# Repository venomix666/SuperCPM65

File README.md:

# SuperCPM65
SNES cartrige for CP/M-65, still an untested work in progress

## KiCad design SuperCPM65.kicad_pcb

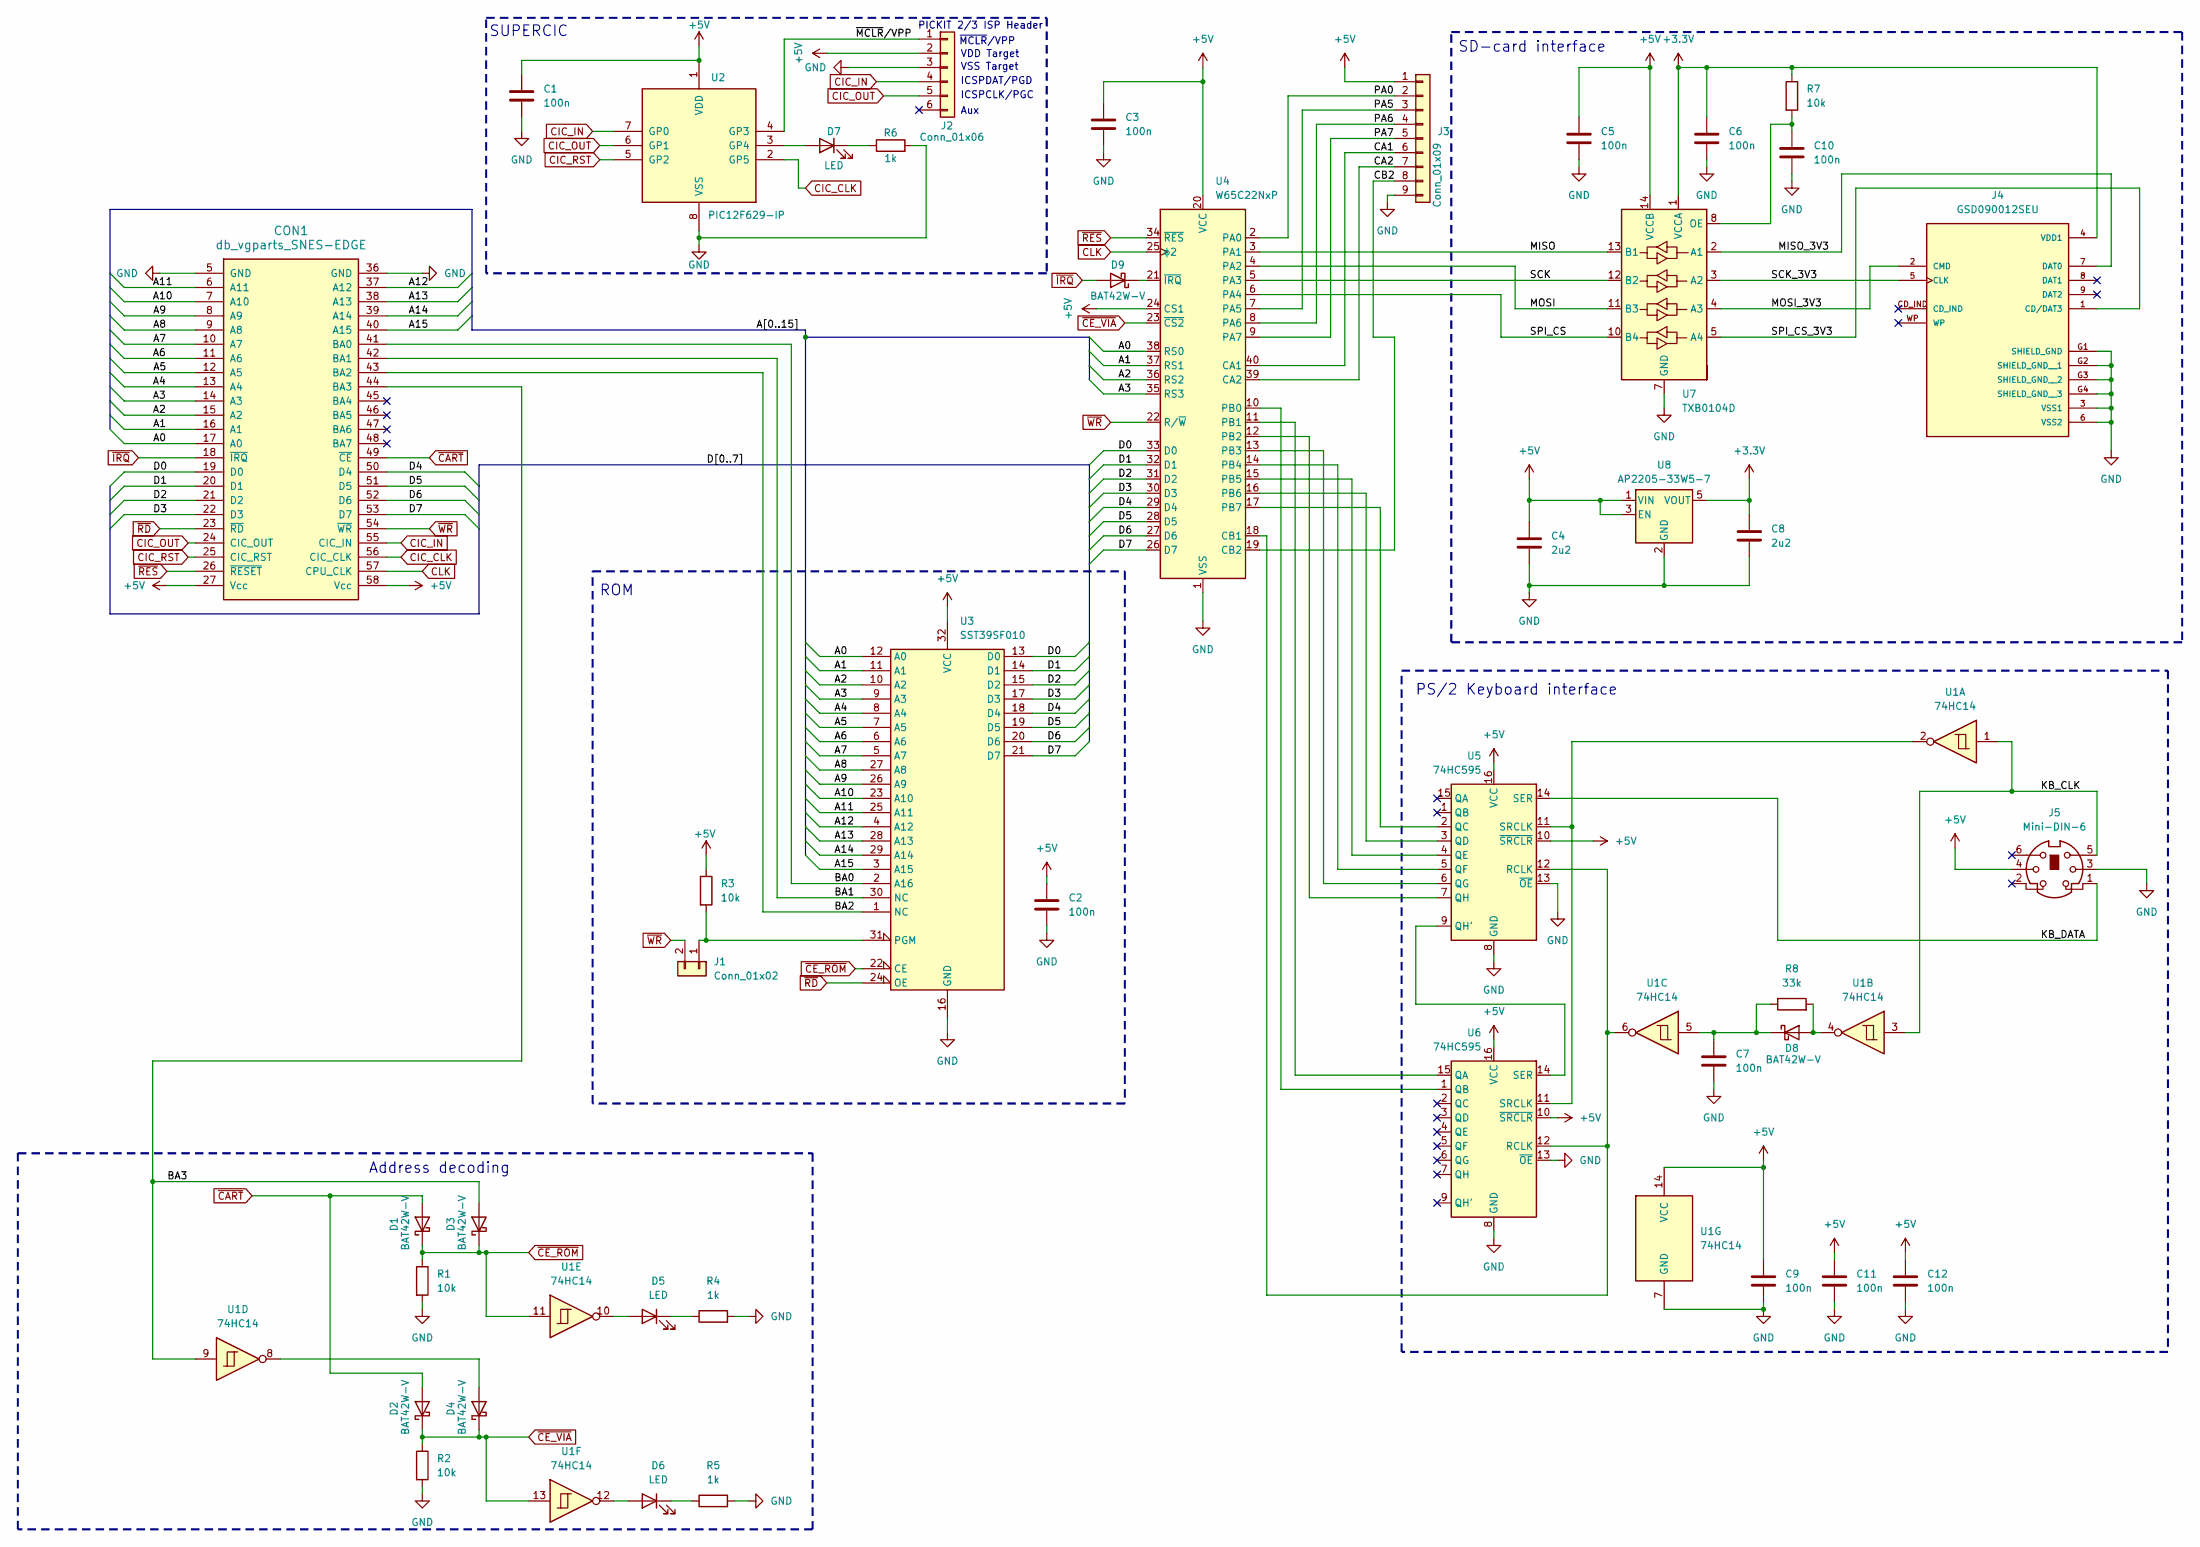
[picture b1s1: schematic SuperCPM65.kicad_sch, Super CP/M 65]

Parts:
C1, C2, C3, C5, C6, C7, C9, C10, C11, C12: 100n; C_0805_2012Metric_Pad1.18x1.45mm_HandSolder
C4, C8: 2u2; C_0805_2012Metric_Pad1.18x1.45mm_HandSolder
CON1: db_vgparts_SNES-EDGE; SNES-EDGE-Bigger
D1, D2, D3, D4, D8, D9: BAT42W-V; D_SOD-123
D5, D6, D7: LED; LED_0805_2012Metric
J1: Conn_01x02; PinHeader_1x02_P2.54mm_Vertical
J2: Conn_01x06; PinHeader_1x06_P2.54mm_Vertical
J3: Conn_01x09; PinHeader_1x09_P2.54mm_Vertical
J4: GSD090012SEU; AMPHENOL_GSD090012SEU; PARTREV E
J5: Mini-DIN-6; TE 5749266-1
R1, R2, R3, R7: 10k; R_0805_2012Metric_Pad1.20x1.40mm_HandSolder
R4, R5, R6: 1k; R_0805_2012Metric_Pad1.20x1.40mm_HandSolder
R8: 33k; R_0805_2012Metric_Pad1.20x1.40mm_HandSolder
U1: 74HC14; SOIC-14_3.9x8.7mm_P1.27mm
U2: PIC12F629-IP; DIP-8_W7.62mm_Socket
U3: SST39SF010; DIP-32_W15.24mm_Socket
U4: W65C22NxP; DIP-40_W15.24mm
U5, U6: 74HC595; SOIC-16_3.9x9.9mm_P1.27mm
U7: TXB0104D; SOIC-14_3.9x8.7mm_P1.27mm
U8: AP2205-33W5-7; SOT-23-5

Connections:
+3.3V: C6.1, C8.1, J4.4 (VDD1), R7.1, U7.1 (VCCA), U8.5 (VOUT)
+5V: C1.1, C2.1, C3.1, C4.1, C5.1, C9.1, C11.1, C12.1, CON1.27 (Vcc), CON1.58 (Vcc), J2.2, J3.1, J5.4, R3.1, U1.14 (VCC), U2.1 (VDD), U3.32 (VCC), U4.20 (VCC), U4.24 (CS1), U5.10 (~SRCLR), U5.16 (VCC), U6.10 (~SRCLR), U6.16 (VCC), U7.14 (VCCB), U8.1 (VIN), U8.3 (EN)
/A0: CON1.17 (A0), U3.12 (A0), U4.38 (RS0)
/A1: CON1.16 (A1), U3.11 (A1), U4.37 (RS1)
/A2: CON1.15 (A2), U3.10 (A2), U4.36 (RS2)
/A3: CON1.14 (A3), U3.9 (A3), U4.35 (RS3)
/A4: CON1.13 (A4), U3.8 (A4)
/A5: CON1.12 (A5), U3.7 (A5)
/A6: CON1.11 (A6), U3.6 (A6)
/A7: CON1.10 (A7), U3.5 (A7)
/A8: CON1.9 (A8), U3.27 (A8)
/A9: CON1.8 (A9), U3.26 (A9)
/A10: CON1.7 (A10), U3.23 (A10)
/A11: CON1.6 (A11), U3.25 (A11)
/A12: CON1.37 (A12), U3.4 (A12)
/A13: CON1.38 (A13), U3.28 (A13)
/A14: CON1.39 (A14), U3.29 (A14)
/A15: CON1.40 (A15), U3.3 (A15)
/BA0: CON1.41 (BA0), U3.2 (A16)
/BA1: CON1.42 (BA1), U3.30 (NC)
/BA2: CON1.43 (BA2), U3.1 (NC)
/BA3: CON1.44 (BA3), D3.2 (A), U1.9
/CA1: J3.6, U4.40 (CA1)
/CA2: J3.7, U4.39 (CA2)
/CB2: J3.8, U4.19 (CB2)
/D0: CON1.19 (D0), U3.13 (D0), U4.33 (D0)
/D1: CON1.20 (D1), U3.14 (D1), U4.32 (D1)
/D2: CON1.21 (D2), U3.15 (D2), U4.31 (D2)
/D3: CON1.22 (D3), U3.17 (D3), U4.30 (D3)
/D4: CON1.50 (D4), U3.18 (D4), U4.29 (D4)
/D5: CON1.51 (D5), U3.19 (D5), U4.28 (D5)
/D6: CON1.52 (D6), U3.20 (D6), U4.27 (D6)
/D7: CON1.53 (D7), U3.21 (D7), U4.26 (D7)
/KB_CLK: J5.5, U1.1, U1.3
/KB_DATA: J5.1, U5.14 (SER)
/MISO: U4.3 (PA1), U7.13 (B1)
/MISO_3V3: J4.7 (DAT0), U7.2 (A1)
/MOSI: U4.4 (PA2), U7.11 (B3)
/MOSI_3V3: J4.2 (CMD), U7.4 (A3)
/PA0: J3.2, U4.2 (PA0)
/PA5: J3.3, U4.7 (PA5)
/PA6: J3.4, U4.8 (PA6)
/PA7: J3.5, U4.9 (PA7)
/SCK: U4.5 (PA3), U7.12 (B2)
/SCK_3V3: J4.5 (CLK), U7.3 (A2)
/SPI_CS: U4.6 (PA4), U7.10 (B4)
/SPI_CS_3V3: J4.1 (CD/DAT3), U7.5 (A4)
/~MCLR/VPP: J2.1, U2.4 (GP3)
CIC_CLK: CON1.56 (CIC_CLK), U2.2 (GP5)
CIC_IN: CON1.55 (CIC_IN), J2.4, U2.7 (GP0)
CIC_OUT: CON1.24 (CIC_OUT), J2.5, U2.6 (GP1)
CIC_RST: CON1.25 (CIC_RST), U2.5 (GP2)
CLK: CON1.57 (CPU_CLK), U4.25 (ϕ2)
GND: C1.2, C2.2, C3.2, C4.2, C5.2, C6.2, C7.2, C8.2, C9.2, C10.2, C11.2, C12.2, CON1.5 (GND), CON1.36 (GND), J2.3, J3.9, J4.3 (VSS1), J4.6 (VSS2), J4.G1 (SHIELD_GND), J4.G2 (SHIELD_GND__1), J4.G3 (SHIELD_GND__2), J4.G4 (SHIELD_GND__3), J5.3, R1.2, R2.2, R4.2, R5.2, R6.2, U1.7 (GND), U2.8 (VSS), U3.16 (GND), U4.1 (VSS), U5.8 (GND), U5.13 (~OE), U6.8 (GND), U6.13 (~OE), U7.7 (GND), U8.2 (GND)
unnamed: D4.2 (A), U1.8
unnamed: D5.2 (A), U1.10
unnamed: D5.1 (K), R4.1
unnamed: D6.2 (A), U1.12
unnamed: D6.1 (K), R5.1
unnamed: D7.2 (A), U2.3 (GP4)
unnamed: D7.1 (K), R6.1
unnamed: D8.2 (A), R8.2, U1.4
unnamed: C7.1, D8.1 (K), R8.1, U1.5
unnamed: D9.1 (K), U4.21 (~IRQ)
unnamed: J1.1, R3.2, U3.31 (PGM)
unnamed: U1.6, U4.18 (CB1), U5.12 (RCLK), U6.12 (RCLK)
unnamed: U4.10 (PB0), U6.1 (QB)
unnamed: U4.11 (PB1), U6.15 (QA)
unnamed: U4.12 (PB2), U5.7 (QH)
unnamed: U4.13 (PB3), U5.6 (QG)
unnamed: U4.14 (PB4), U5.5 (QF)
unnamed: U4.15 (PB5), U5.4 (QE)
unnamed: U4.16 (PB6), U5.3 (QD)
unnamed: U4.17 (PB7), U5.2 (QC)
unnamed: U5.9 (QH'), U6.14 (SER)
unnamed: U1.2, U5.11 (SRCLK), U6.11 (SRCLK)
unnamed: C10.1, R7.2, U7.8 (OE)
~CART: CON1.49 (~CE), D1.2 (A), D2.2 (A)
~CE_ROM: D1.1 (K), D3.1 (K), R1.1, U1.11, U3.22 (CE)
~CE_VIA: D2.1 (K), D4.1 (K), R2.1, U1.13, U4.23 (~CS2)
~IRQ: CON1.18 (~IRQ), D9.2 (A)
~RD: CON1.23 (~RD), U3.24 (OE)
~RES: CON1.26 (~RESET), U4.34 (~RES)
~WR: CON1.54 (~WR), J1.2, U4.22 (R/~W)

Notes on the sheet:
SUPERCIC
Address decoding
SD-card interface
~{MCLR}/VPP
ROM
VDD Target
PS/2 Keyboard interface
VSS Target
ICSPCLK/PGC
Aux
PICKIT 2/3 ISP Header
ICSPDAT/PGD

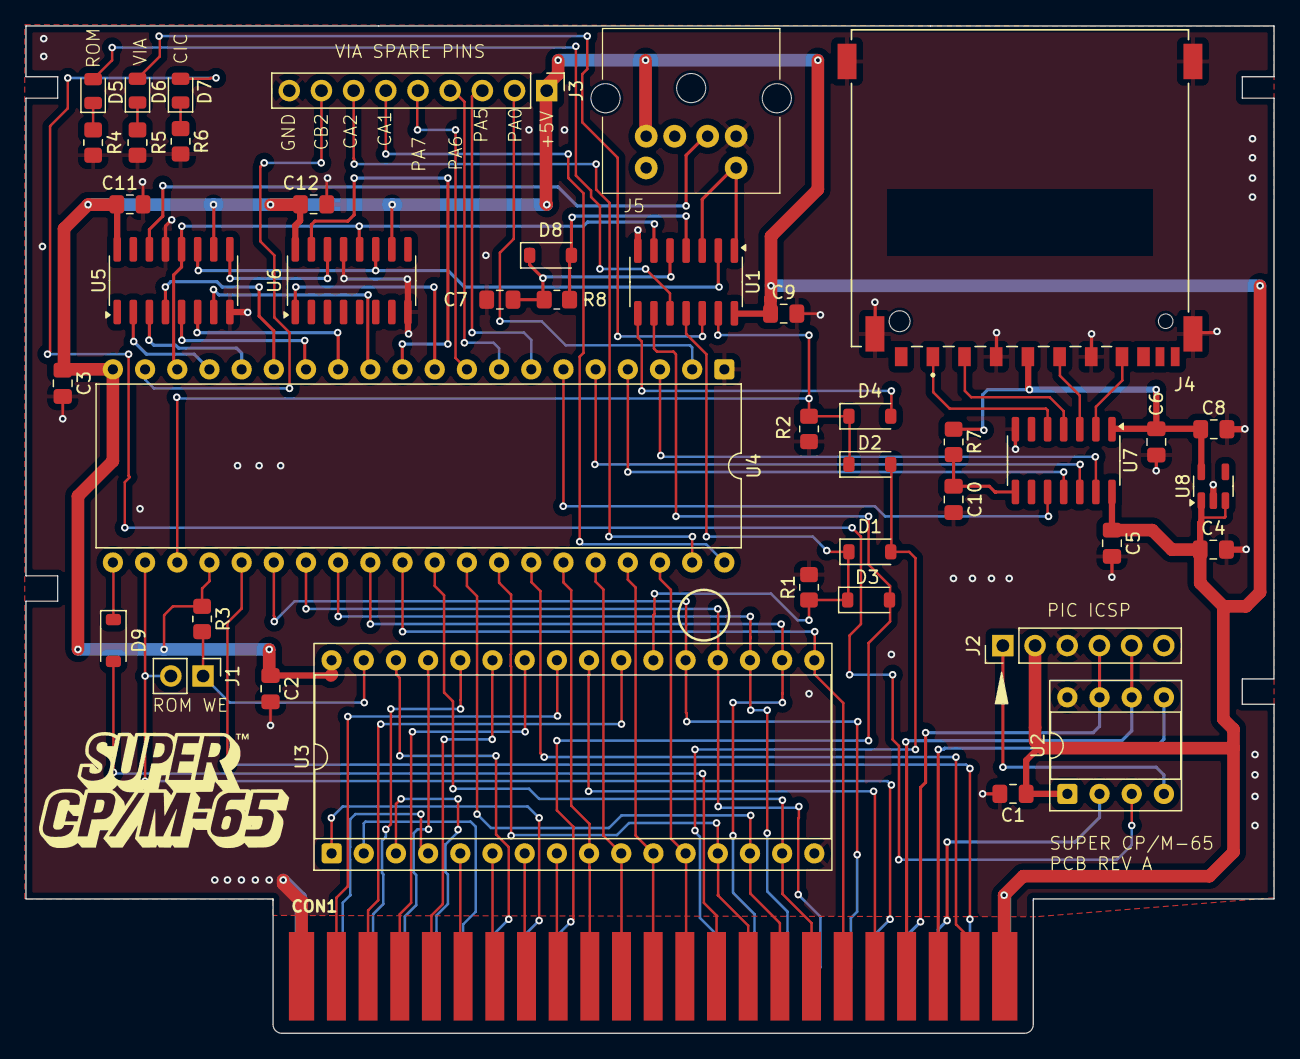
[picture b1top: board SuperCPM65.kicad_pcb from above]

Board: 2 copper layers, 98.5 x 79.5 mm, 43 parts (0 on the bottom side), 84 nets.

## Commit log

2025-03-16 Initial add of project files
2025-03-16 Updated the 3D model for the socketed ROM
2025-03-16 Routing updates
2025-03-16 Fixed some 3D model issues and socketed the PIC
2025-03-17 Added LEDs for CE signals, header for leftover VIA I/Os, changed addressing to allow larger Flash memory and added a jumper for Flash memory write enable
2025-03-17 Reset component annotation as some components were removed
2025-03-17 Continued routing, more or less completed
2025-03-17 Updated pdf schematics
2025-03-17 Updated BOM
2025-03-18 Added stitching vias to improve ground plane impedance and fill ratio
2025-03-18 Silkscreen cleanup etc.
2025-03-18 Added gerber files for Rev A
2025-03-18 Added assembly drawings and moved PDF schematics to its own directory
2025-03-20 Added more signals to VIA spare header. Added diode to IRQ line. Changed all diodes to schottky
2025-03-20 Imported schematic updated, placed LEDs at top, minor rearrangement
2025-04-09 Updated gerbers and PDF schematics
2025-04-10 Minor cleanup
